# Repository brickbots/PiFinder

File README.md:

# PiFinder™
A plate solving telescope finder based around a Raspberry PI, imx296 camera, and custom UI 'hat'

For an overview of what the PiFinder™ is and how it came to be visit the official project website at [PiFinder.io](https://www.pifinder.io/build-yours) 

The PiFinder™ uses the [Cedar Detect](https://github.com/smroid/cedar-detect) and
[Cedar Solve](https://github.com/smroid/cedar-solve) libraries by
[smroid](https://github.com/smroid). Cedar Solve is licensed under Apache-2.0.

**Cedar Detect** is published under the Functional Source License (`FSL-1.1-MIT`),
which permits broad non-commercial use but excludes commercial uses that compete
with Cedar Detect. Because the PiFinder™ is also offered commercially, it bundles
and distributes the Cedar Detect binaries under a **separate license granted
expressly by the copyright holder** — not under the public FSL terms. The prebuilt
binaries live in [`bin/`](./bin/); see [`bin/README.md`](./bin/README.md) for the
full licensing details and a copy of the Cedar Detect license. Note this is
distinct from the PiFinder project's own GPL-3.0 [`LICENSE`](./LICENSE).

Thank you to [smroid](https://github.com/smroid) for all your support of the PiFinder project!

The PiFinder™ is my attempt to improve my time at my telescope.  I don't get nearly enough of it and I want to enjoy it as much as possible.  So after years of observing with paper charts and, later, a Nexus DSC here is what I felt I was missing:
* **Reliable telescope positioning:**  The Nexus DSC is great, but my scope just isn't built for solid encoder integration.  The slop in the way I have to couple the encoders means poor pointing accuracy.
* **Easy setup:**  The Nexus DSC needs multi-star alignment to understand how the encoders map to the sky.  The process is not terrible, but I'd like to avoid it.
* **Good push-to functionality**:  This is one place the Nexus DSC shines... if it's well aligned.  The catalog system is okay, and once you select and object the screen is clear and helpful to get the telescope pointed correctly.
* **Observation logging**:  I like to keep track of what I see each night.  I don't often sketch, just record what I saw when, with what eyepiece and some basic info about the experience.  If I could do this right at the eyepiece, that'd save time.

My hope is that other people will find this combination of functionality useful, will build their own PiFinder™ and help the whole project improve by making suggestions and potentially contributing to the software.  It's a pretty easy build with off the shelf parts and beginner friendly soldering.  

## Features
* Zero setup: Just turn it on and point it at the sky!  
* Accurate pointing: Onboard GPS determines location and time while the camera determines where the scope is pointing.  Inertial Measurement Unit tracks scope motion and updates sky position between camera solves
* Self-contained:  Includes catalog search/filtering, sky/object charting, push-to guidance and logging all via the screen and keypad on the unit.
* Dark site friendly:  Red OLED screen and soft backlit keys have wide brightness adjustment, right down to 'off'. No need for bright cell phones or tablets
* Easy access: Can be mounted by the eyepiece just like a finder.
- Wifi Access Point / SkySafari Integration:  The PiFinder™ can act as a WIFI access point to connect your tablet or phone to sync SkySafari or other planetarium software with your scope.

## Build Your Own
The PiFinder™ is fully open-source hardware and software.  You can order PCB's and 3d print the case with the files in this repo and order all the parts from the [parts List](https://pifinder.readthedocs.io/en/release/BOM.html).

If you would like pre-assembled units, kits or other items to jump start your PiFinder™ journey, visit [PiFinder.io](https://www.pifinder.io/build-pifinder) to see what's available and place an order.

## Docs

* [Quick Start](https://pifinder.readthedocs.io/en/release/quick_start.html)
* [User Manual](https://pifinder.readthedocs.io/en/release/user_guide.html)
* [Parts List](https://pifinder.readthedocs.io/en/release/BOM.html)
* [Build Guide](https://pifinder.readthedocs.io/en/release/build_guide.html)
* [Software Setup](https://pifinder.readthedocs.io/en/release/software.html)
* [Developer Guide](https://pifinder.readthedocs.io/en/release/dev_guide.html)

## Releases and Updates

If you are using a PiFinder, I recommend you watch releases in this repo.  Click the 'Watch' button up at the top right of the page, choose 'Custom' and then 'Releases' to make sure you don't miss any new features!

If you'd like to learn more about how it works, and potentially build your own, everything you need should be here.  I recommend starting with the [User Manual](https://pifinder.readthedocs.io/en/release/user_guide.html) and then checking out the build process using the links below.

## Discord
Join the  [PiFinder™ Discord server](https://discord.gg/Nk5fHcAtWD) for support with your build, usage questions, and suggestions for improvement.

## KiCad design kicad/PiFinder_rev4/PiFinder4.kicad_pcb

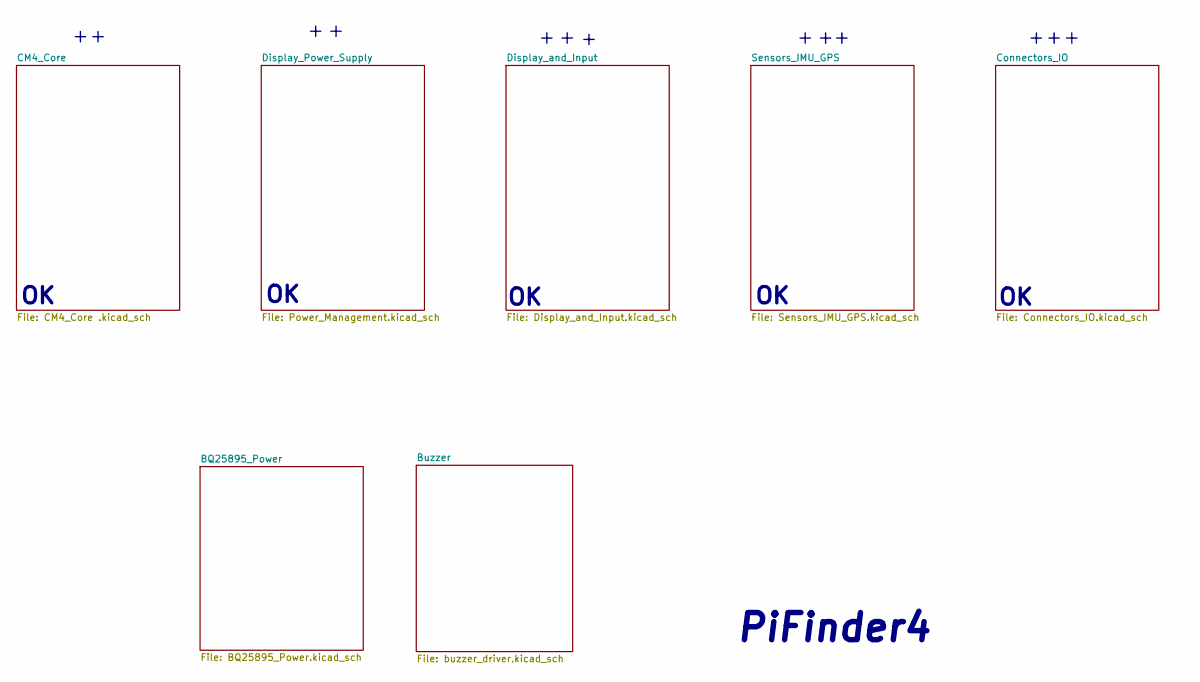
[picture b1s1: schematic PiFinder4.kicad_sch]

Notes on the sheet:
PiFinder4

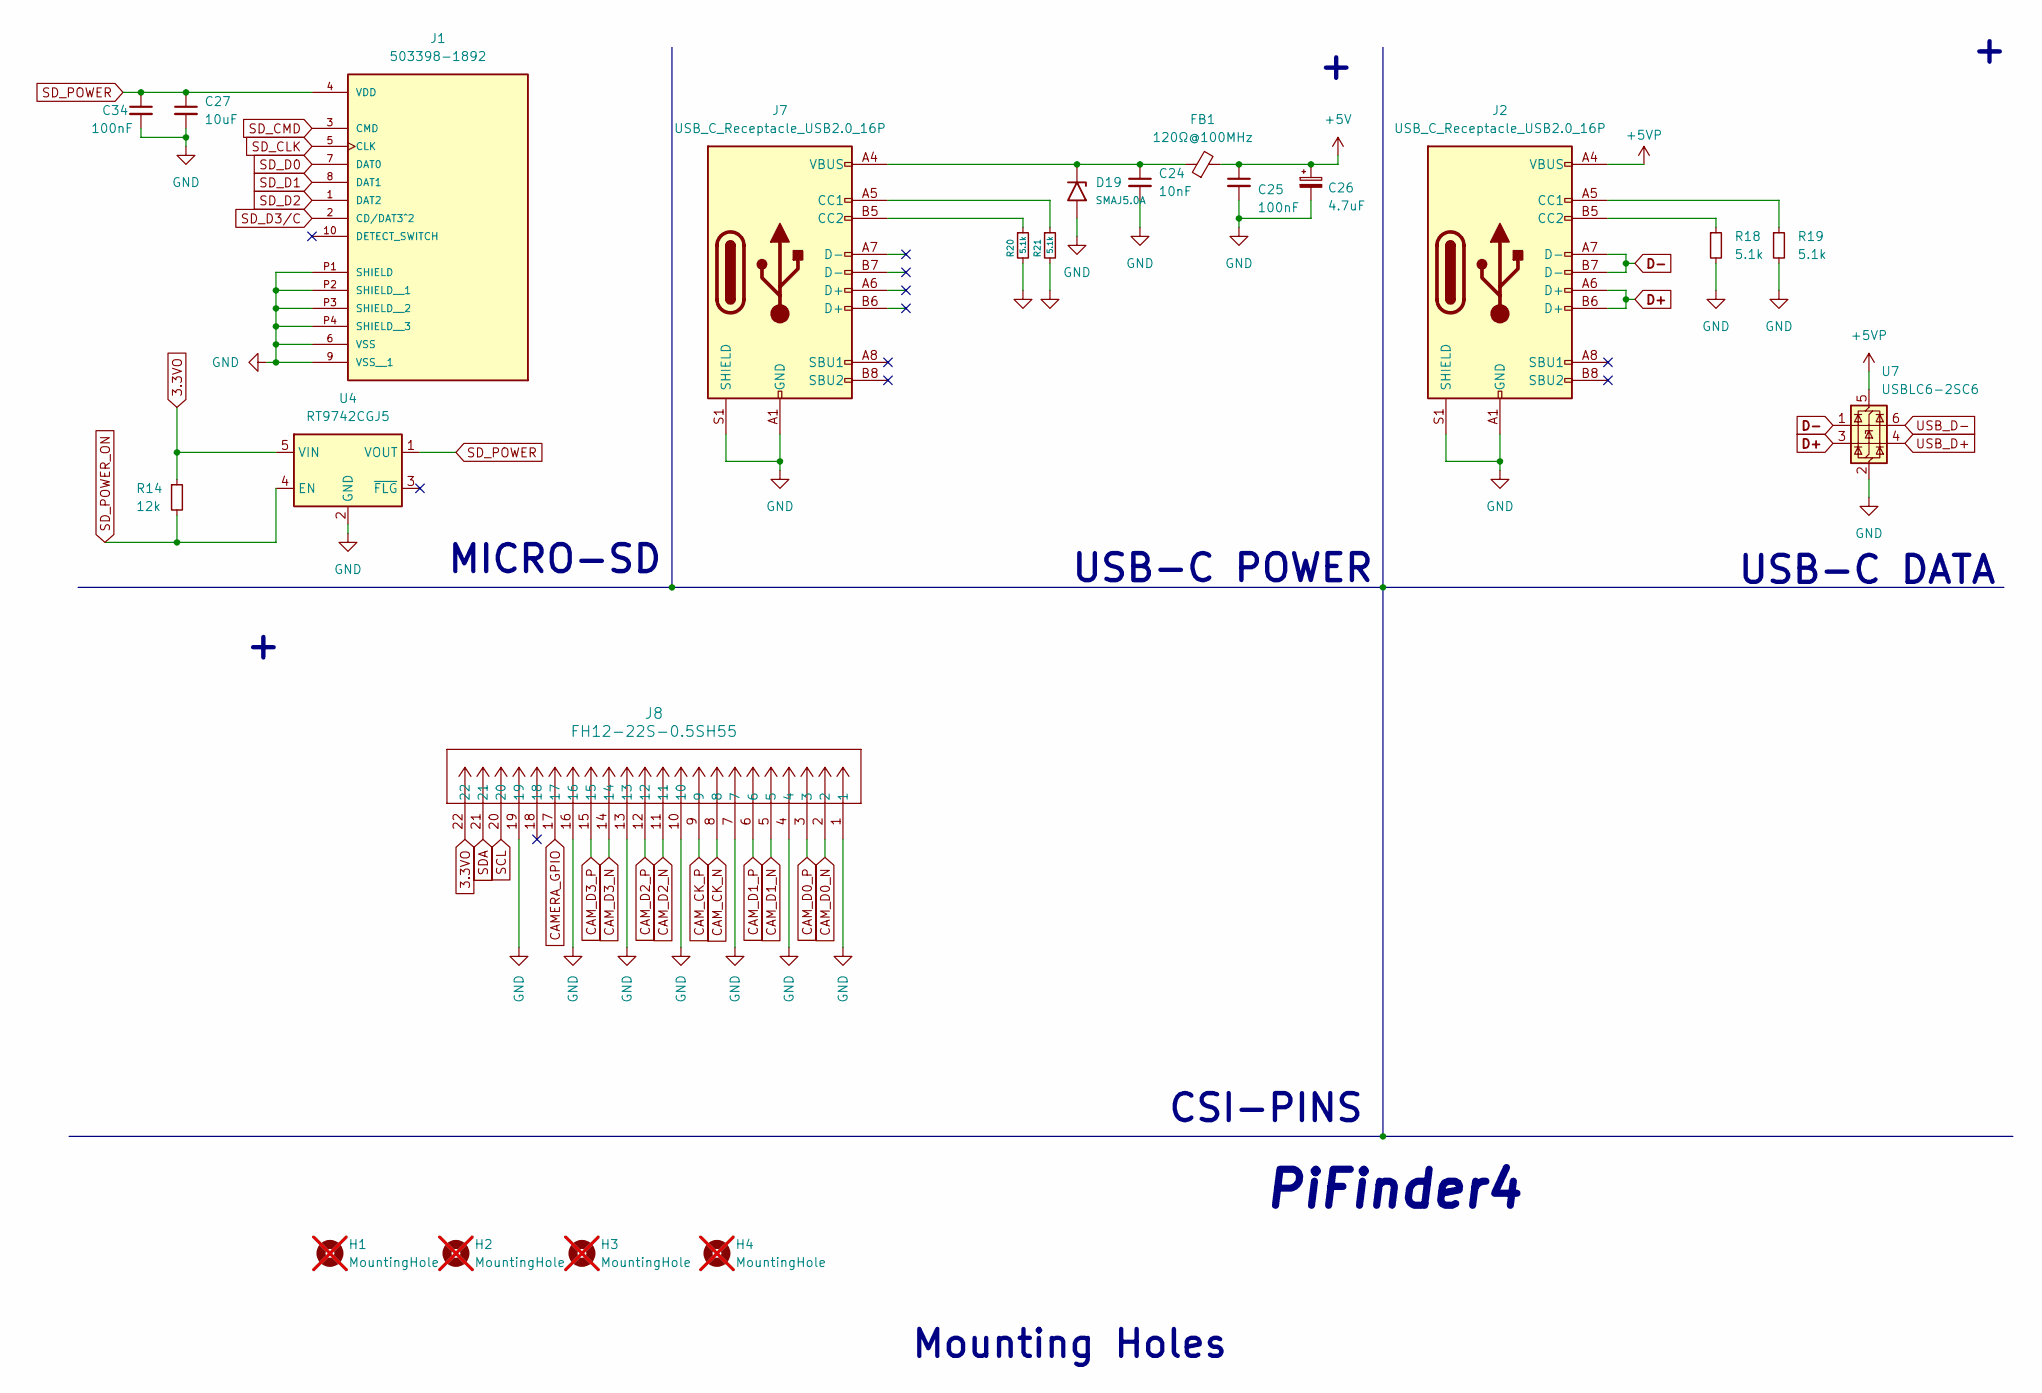
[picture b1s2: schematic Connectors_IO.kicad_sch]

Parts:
C24: 10nF; C_0402_1005Metric; LCSC C15195
C25, C34: 100nF; C_0603_1608Metric; LCSC C14663
C26: 4.7uF; CP_Elec_4x5.4; LCSC C970651
C27: 10uF; C_0805_2012Metric; LCSC C15850
D19: SMAJ5.0A; D_SMA; LCSC C10758
FB1: 120Ω@100MHz; L_1206_3216Metric; LCSC C85841
H1, H2, H3, H4: MountingHole; MountingHole_2.5mm; not fitted
J1: 503398-1892; MOLEX_503398-1892; PARTREV 0; LCSC C428492
J2, J7: USB_C_Receptacle_USB2.0_16P; USB_C_Receptacle_HCTL_HC-TYPE-C-16P-01A; LCSC C165948
J8: FH12-22S-0.5SH55; CONN_FH12-22S-0.5SH55_HIR; LCSC C597981
R14: 12k; R_0402_1005Metric; LCSC C25752
R18, R19, R20, R21: 5.1k; R_0402_1005Metric; LCSC C25905
U4: RT9742CGJ5; TSOT-23-5; LCSC C424402
U7: USBLC6-2SC6; SOT-23-6; LCSC C2687116

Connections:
3.3VO: J8.22, R14.1, U4.5 (VIN); also elsewhere on the board
+5V: C25.1, C26.1, FB1.2; also elsewhere on the board
+5VP: J2.A4 (VBUS), J2.A9 (VBUS), J2.B4 (VBUS), J2.B9 (VBUS), U7.5 (VBUS); also elsewhere on the board
CAMERA_GPIO: J8.17; also elsewhere on the board
CAM_CK_N: J8.8; also elsewhere on the board
CAM_CK_P: J8.9; also elsewhere on the board
CAM_D0_N: J8.2; also elsewhere on the board
CAM_D0_P: J8.3; also elsewhere on the board
CAM_D1_N: J8.5; also elsewhere on the board
CAM_D1_P: J8.6; also elsewhere on the board
CAM_D2_N: J8.11; also elsewhere on the board
CAM_D2_P: J8.12; also elsewhere on the board
CAM_D3_N: J8.14; also elsewhere on the board
CAM_D3_P: J8.15; also elsewhere on the board
D+: J2.A6 (D+), J2.B6 (D+), U7.3 (I/O2)
D-: J2.A7 (D-), J2.B7 (D-), U7.1 (I/O1)
GND: C24.2, C25.2, C26.2, C27.2, C34.2, D19.2 (A2), J1.6 (VSS), J1.9 (VSS__1), J1.P1 (SHIELD), J1.P2 (SHIELD__1), J1.P3 (SHIELD__2), J1.P4 (SHIELD__3), J2.A1 (GND), J2.A12 (GND), J2.B1 (GND), J2.B12 (GND), J2.S1 (SHIELD), J7.A1 (GND), J7.A12 (GND), J7.B1 (GND), J7.B12 (GND), J7.S1 (SHIELD), J8.1, J8.4, J8.7, J8.10, J8.13, J8.16, J8.19, R18.2, R19.2, R20.2, R21.2, U4.2 (GND), U7.2 (GND); also elsewhere on the board
unnamed: C24.1, D19.1 (A1), FB1.1, J7.A4 (VBUS), J7.A9 (VBUS), J7.B4 (VBUS), J7.B9 (VBUS)
unnamed: J2.A5 (CC1), R19.1
unnamed: J2.B5 (CC2), R18.1
unnamed: J7.A5 (CC1), R21.1
unnamed: J7.B5 (CC2), R20.1
SCL: J8.20; also elsewhere on the board
SDA: J8.21; also elsewhere on the board
SD_CLK: J1.5 (CLK); also elsewhere on the board
SD_CMD: J1.3 (CMD); also elsewhere on the board
SD_D0: J1.7 (DAT0); also elsewhere on the board
SD_D1: J1.8 (DAT1); also elsewhere on the board
SD_D2: J1.1 (DAT2); also elsewhere on the board
SD_D3/C: J1.2 (CD/DAT3^2); also elsewhere on the board
SD_POWER: C27.1, C34.1, J1.4 (VDD), U4.1 (VOUT)
SD_POWER_ON: R14.2, U4.4 (EN); also elsewhere on the board
USB_D+: U7.4 (I/O2); also elsewhere on the board
USB_D-: U7.6 (I/O1); also elsewhere on the board

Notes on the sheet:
CSI-PINS
USB-C DATA
PiFinder4
USB-C POWER
MICRO-SD
Mounting Holes

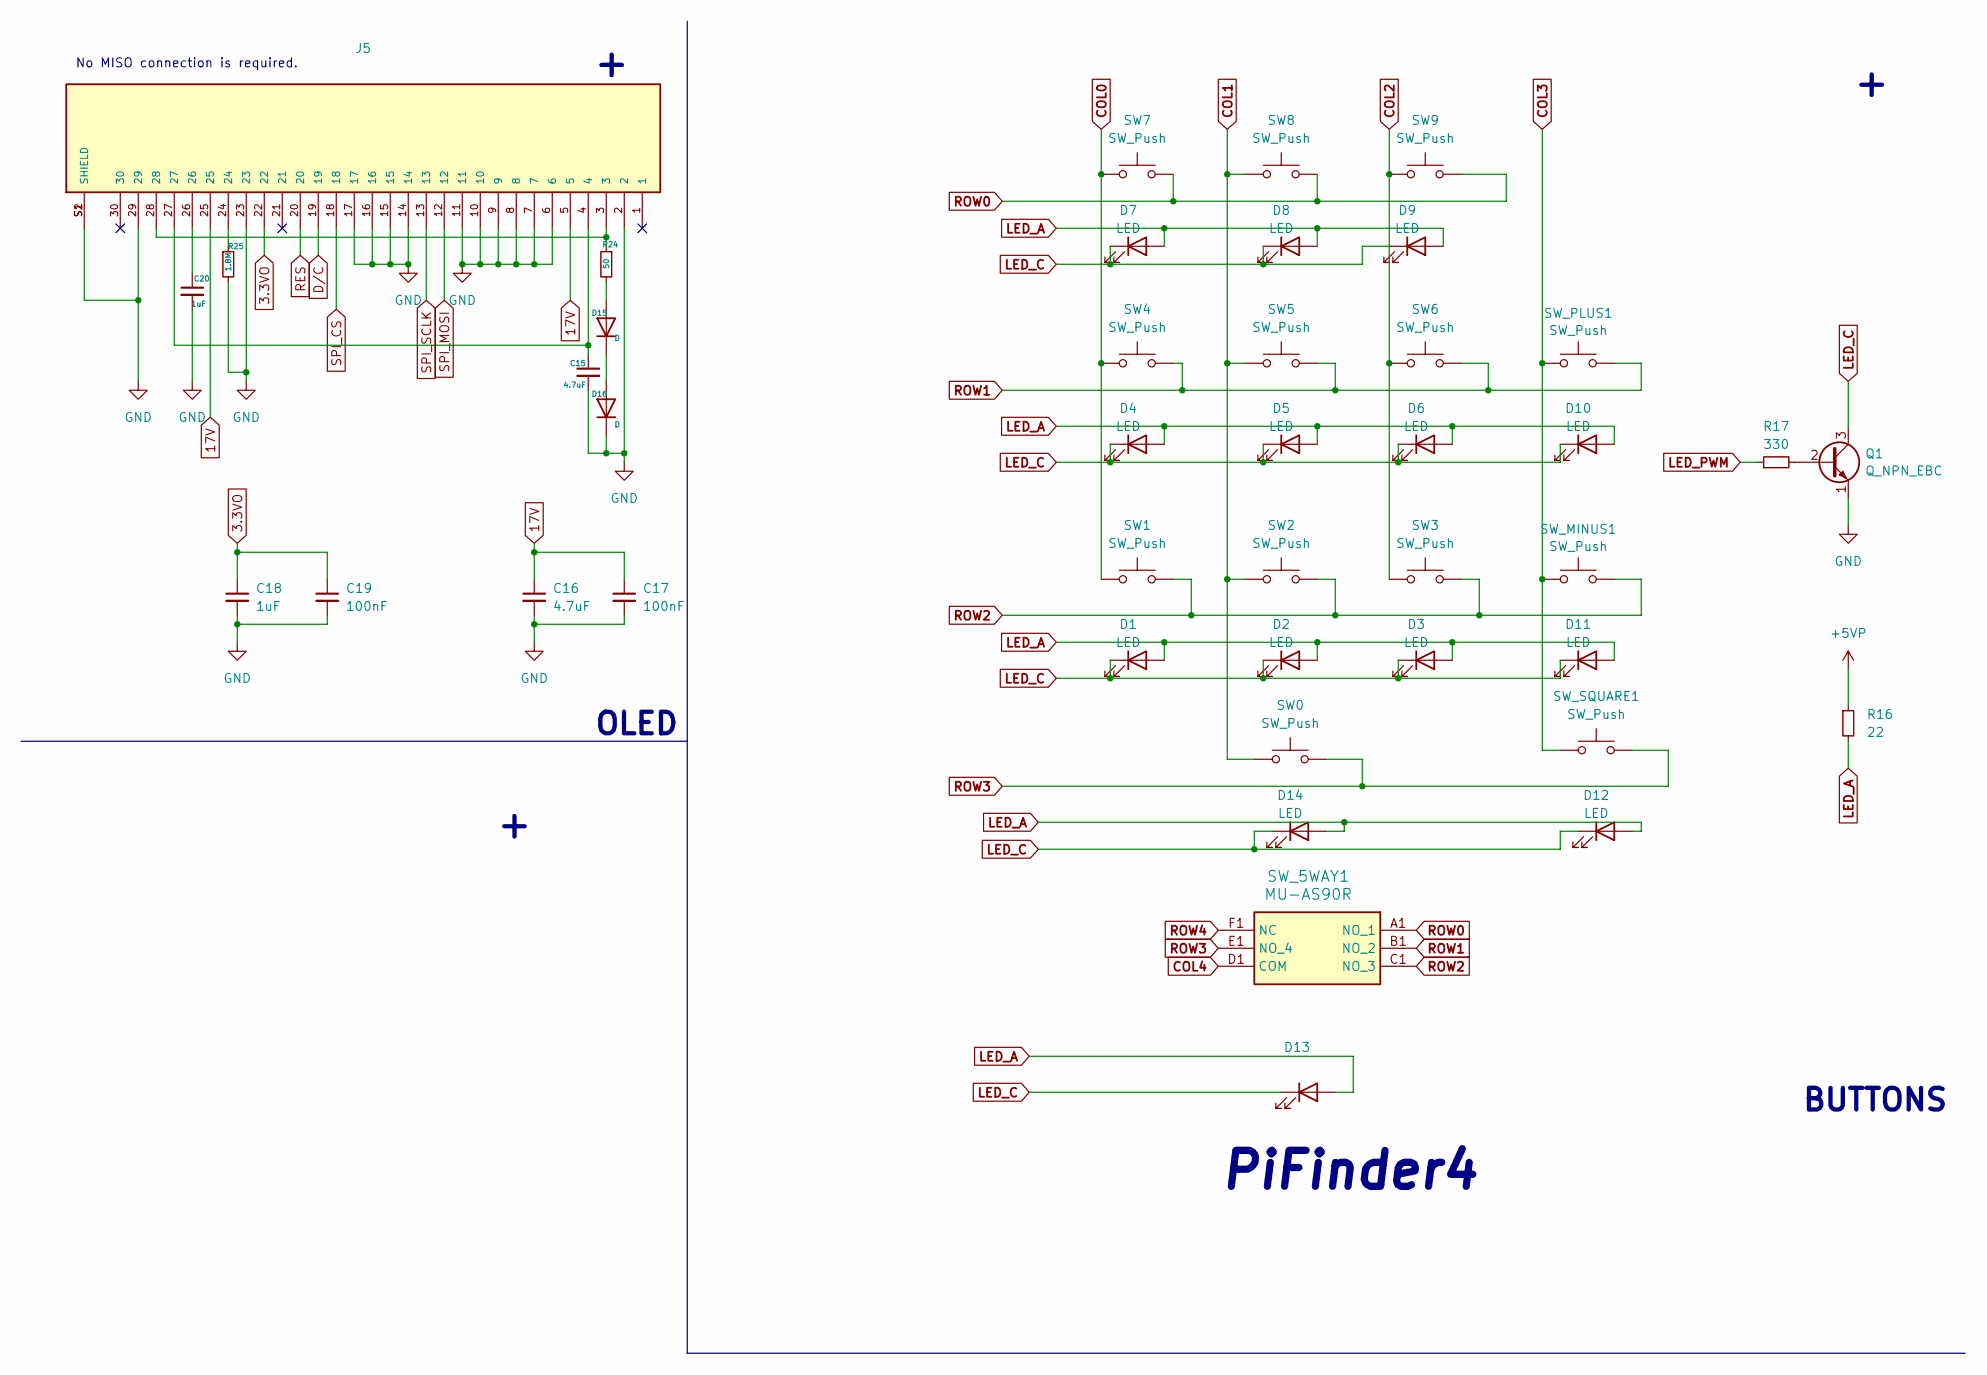
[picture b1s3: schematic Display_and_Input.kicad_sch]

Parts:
C15, C16: 4.7uF; C_1206_3216Metric; LCSC C29823
C17, C19: 100nF; C_0603_1608Metric; LCSC C14663
C18, C20: 1uF; C_0603_1608Metric; LCSC C15849
D1, D2, D3, D4, D5, D6, D7, D8, D9, D10, D11, D12, D13, D14: LED; LED_1210_3225Metric; LCSC C264578
D15, D16: D; D_SOD-123; LCSC C81598
J5: TE_3-1734592-0; PARTREV C; LCSC C375905
Q1: Q_NPN_EBC; PF_SOT-23-NPN; LCSC C280842
R16: 22; R_0402_1005Metric; LCSC C25092
R17: 330; R_0402_1005Metric; LCSC C25104
R24: 50; R_0603_1608Metric; LCSC C844932
R25: 1.8M; R_0402_1005Metric; LCSC C38587
SW0, SW1, SW2, SW3, SW4, SW5, SW6, SW7, SW8, SW9: SW_Push; SW_Push_6x6mm_SMT_withhole_tight; LCSC C4364377
SW_5WAY1: MU-AS90R; MUAS70R; Mouser Part Number 642-MU-AS70R; LCSC C38516684
SW_MINUS1: SW_Push; SW_Push_6x6mm_SMT_withhole_tight; LCSC C4364377
SW_PLUS1: SW_Push; SW_Push_6x6mm_SMT_withhole_tight; LCSC C4364377
SW_SQUARE1: SW_Push; SW_Push_6x6mm_SMT_withhole_tight; LCSC C4364377

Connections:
3.3VO: C18.1, C19.1, J5.22; also elsewhere on the board
17V: C16.1, C17.1, J5.5, J5.25; also elsewhere on the board
+5VP: R16.1; also elsewhere on the board
COL0: SW1.1, SW4.1, SW7.1; also elsewhere on the board
COL1: SW0.1, SW2.1, SW5.1, SW8.1; also elsewhere on the board
COL2: SW3.1, SW6.1, SW9.1; also elsewhere on the board
COL3: SW_MINUS1.1, SW_PLUS1.1, SW_SQUARE1.1; also elsewhere on the board
COL4: SW_5WAY1.D1 (COM); also elsewhere on the board
D/C: J5.19; also elsewhere on the board
GND: C15.2, C16.2, C17.2, C18.2, C19.2, C20.2, D16.1 (K), J5.2, J5.6, J5.7, J5.8, J5.9, J5.10, J5.11, J5.14, J5.15, J5.16, J5.17, J5.23, J5.29, J5.S1 (SHIELD), J5.S2 (SHIELD), Q1.1 (E), R25.2; also elsewhere on the board
LED_A: D1.2 (A), D2.2 (A), D3.2 (A), D4.2 (A), D5.2 (A), D6.2 (A), D7.2 (A), D8.2 (A), D9.2 (A), D10.2 (A), D11.2 (A), D12.2 (A), D13.2 (A), D14.2 (A), R16.2
LED_C: D1.1 (K), D2.1 (K), D3.1 (K), D4.1 (K), D5.1 (K), D6.1 (K), D7.1 (K), D8.1 (K), D9.1 (K), D10.1 (K), D11.1 (K), D12.1 (K), D13.1 (K), D14.1 (K), Q1.3 (C)
LED_PWM: R17.1; also elsewhere on the board
unnamed: C15.1, J5.4, J5.27
unnamed: C20.1, J5.26
unnamed: D15.2 (A), R24.2
unnamed: D15.1 (K), D16.2 (A)
unnamed: J5.24, R25.1
unnamed: J5.3, J5.28, R24.1
unnamed: Q1.2 (B), R17.2
RES: J5.20; also elsewhere on the board
ROW0: SW7.2, SW8.2, SW9.2, SW_5WAY1.A1 (NO_1); also elsewhere on the board
ROW1: SW4.2, SW5.2, SW6.2, SW_5WAY1.B1 (NO_2), SW_PLUS1.2; also elsewhere on the board
ROW2: SW1.2, SW2.2, SW3.2, SW_5WAY1.C1 (NO_3), SW_MINUS1.2; also elsewhere on the board
ROW3: SW0.2, SW_5WAY1.E1 (NO_4), SW_SQUARE1.2; also elsewhere on the board
ROW4: SW_5WAY1.F1 (NC); also elsewhere on the board
SPI_CS: J5.18; also elsewhere on the board
SPI_MOSI: J5.12; also elsewhere on the board
SPI_SCLK: J5.13; also elsewhere on the board

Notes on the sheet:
No MISO connection is required.
PiFinder4
BUTTONS
OLED

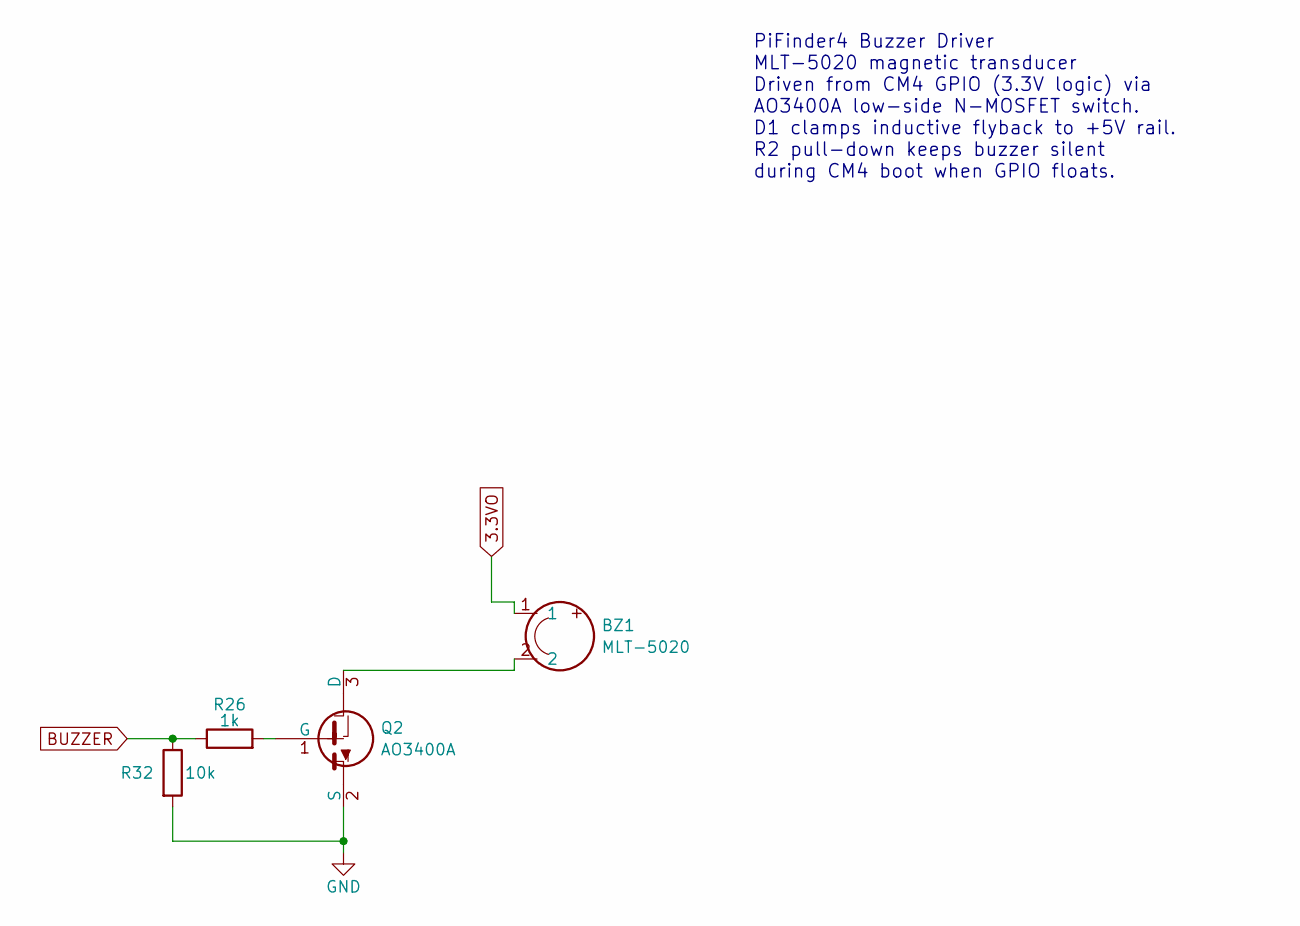
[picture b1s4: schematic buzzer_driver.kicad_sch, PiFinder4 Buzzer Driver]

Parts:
BZ1: MLT-5020; MagneticBuzzer_HuaWha_MLT-5020; LCSC C94598
Q2: AO3400A; SOT-23; LCSC C20917
R26: 1k; R_0402_1005Metric; LCSC C11702
R32: 10k; R_0402_1005Metric; LCSC C25744

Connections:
3.3VO: BZ1.1; also elsewhere on the board
BUZZER: R26.1, R32.1; also elsewhere on the board
GND: Q2.2 (S), R32.2; also elsewhere on the board
unnamed: BZ1.2, Q2.3 (D)
unnamed: Q2.1 (G), R26.2

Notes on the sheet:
PiFinder4 Buzzer Driver MLT-5020 magnetic transducer Driven from CM4 GPIO (3.3V logic) via AO3400A low-side N-MOSFET switch. D1 clamps inductive flyback to +5V rail. R2 pull-down keeps buzzer silent during CM4 boot when GPIO floats.

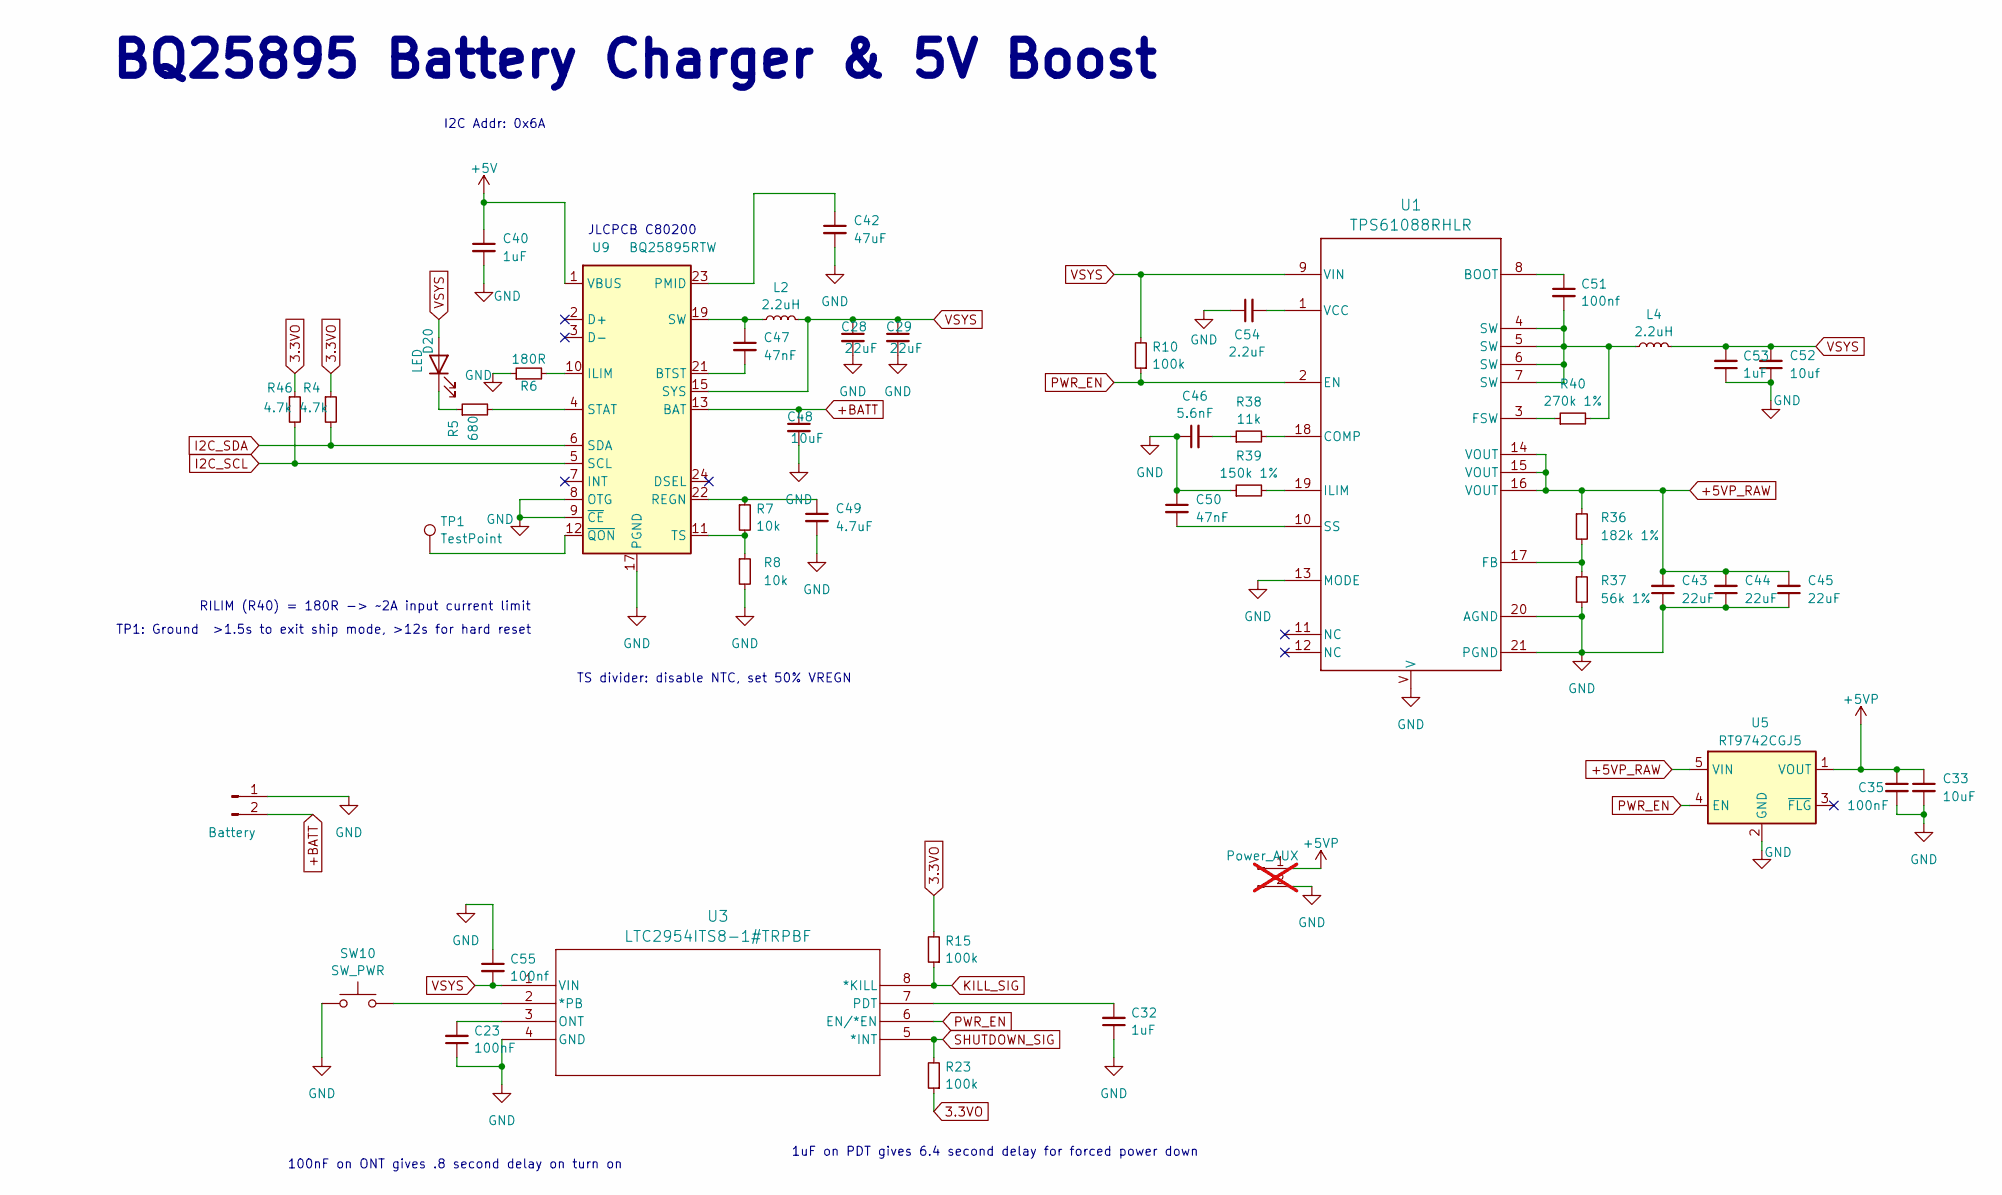
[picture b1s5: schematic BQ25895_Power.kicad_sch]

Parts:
C23, C35: 100nF; C_0603_1608Metric; LCSC C14663
C28, C29, C43, C44, C45: 22uF; C_0805_2012Metric; LCSC C45783
C32, C40, C53: 1uF; C_0603_1608Metric; LCSC C15849
C33: 10uF; C_0805_2012Metric; LCSC C15850
C42: 47uF; C_1206_3216Metric; LCSC C403725
C46: 5.6nF; C_0603_1608Metric; LCSC C107095
C47, C50: 47nF; C_0603_1608Metric; LCSC C1622
C48: 10uF; C_0603_1608Metric; LCSC C96446
C49: 4.7uF; C_0603_1608Metric; LCSC C19666
C51, C55: 100nf; C_0603_1608Metric; LCSC C14663
C52: 10uf; C_0805_2012Metric; LCSC C15850
C54: 2.2uF; C_0603_1608Metric; LCSC C23630
D20: LED; LED_1210_3225Metric; LCSC C264578
J3: Power_AUX; PinHeader_1x02_P2.54mm_Vertical; LCSC C160352; not fitted
J4: Battery; JST_PH_B2B-PH-SM4-TB_1x02-1MP_P2.00mm_Vertical; LCSC C160352
L2, L4: 2.2uH; L_Coilcraft_XAL4020-XXX; LCSC C3151182
R4, R46: 4.7k; R_0402_1005Metric; LCSC C25900
R5: 680; R_0402_1005Metric; LCSC C137948
R6: 180R; R_0402_1005Metric; LCSC C138045
R7, R8: 10k; R_0402_1005Metric; LCSC C25744
R10, R15, R23: 100k; R_0402_1005Metric; LCSC C25741
R36: 182k 1%; R_0402_1005Metric; LCSC C5159679
R37: 56k 1%; R_0402_1005Metric; LCSC C114756
R38: 11k; R_0402_1005Metric; LCSC C138063
R39: 150k 1%; R_0402_1005Metric; LCSC C2909320
R40: 270k 1%; R_0402_1005Metric; LCSC C25770
SW10: SW_PWR; SW_Push_6x6mm_SMT_withhole_tight; LCSC C4364377
TP1: TestPoint
U1: TPS61088RHLR; RHL0020A; LCSC C87357
U3: LTC2954ITS8-1#TRPBF; TSOT-23_TS8_LIT; LCSC C683782
U5: RT9742CGJ5; TSOT-23-5; LCSC C424402
U9: BQ25895RTW; Texas_RTW_WQFN-24-1EP_4x4mm_P0.5mm_EP2.7x2.7mm_ThermalVias; LCSC C80200

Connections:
3.3VO: R4.1, R15.2, R23.1, R46.1; also elsewhere on the board
+5V: C40.1, U9.1 (VBUS); also elsewhere on the board
+5VP: C33.1, C35.1, J3.1, U5.1 (VOUT); also elsewhere on the board
+5VP_RAW: C43.2, C44.2, C45.2, R36.1, U1.14 (VOUT), U1.15 (VOUT), U1.16 (VOUT), U5.5 (VIN)
+BATT: C48.1, J4.2, U9.13 (BAT), U9.14 (BAT)
GND: C23.1, C28.2, C29.2, C32.1, C33.2, C35.2, C40.2, C42.2, C43.1, C44.1, C45.1, C46.1, C48.2, C49.2, C50.1, C52.1, C53.1, C54.1, C55.1, J3.2, J4.1, R6.1, R8.2, R37.2, R39.1, SW10.1, U1.13 (MODE), U1.20 (AGND), U1.21 (PGND), U1.V, U3.4 (GND), U5.2 (GND), U9.8 (OTG), U9.9 (~CE), U9.17 (PGND), U9.18 (PGND), U9.25 (PGND); also elsewhere on the board
I2C_SCL: R46.2, U9.5 (SCL); also elsewhere on the board
I2C_SDA: R4.2, U9.6 (SDA); also elsewhere on the board
KILL_SIG: R15.1, U3.8 (*KILL); also elsewhere on the board
unnamed: C46.2, R38.1
unnamed: C47.1, L2.1, U9.19 (SW), U9.20 (SW)
unnamed: C51.2, L4.1, R40.2, U1.4 (SW), U1.5 (SW), U1.6 (SW), U1.7 (SW)
unnamed: D20.1 (K), R5.1
unnamed: C51.1, U1.8 (BOOT)
unnamed: R38.2, U1.18 (COMP)
unnamed: R36.2, R37.1, U1.17 (FB)
unnamed: R40.1, U1.3 (FSW)
unnamed: R39.2, U1.19 (ILIM)
unnamed: C50.2, U1.10 (SS)
unnamed: C54.2, U1.1 (VCC)
unnamed: SW10.2, U3.2 (*PB)
unnamed: C23.2, U3.3 (ONT)
unnamed: C32.2, U3.7 (PDT)
unnamed: C47.2, U9.21 (BTST)
unnamed: R6.2, U9.10 (ILIM)
unnamed: C42.1, U9.23 (PMID)
unnamed: C49.1, R7.1, U9.22 (REGN)
unnamed: R5.2, U9.4 (STAT)
unnamed: R7.2, R8.1, U9.11 (TS)
unnamed: TP1.1, U9.12 (~QON)
PWR_EN: R10.1, U1.2 (EN), U3.6 (EN/*EN), U5.4 (EN)
SHUTDOWN_SIG: R23.2, U3.5 (*INT); also elsewhere on the board
VSYS: C28.1, C29.1, C52.2, C53.2, C55.2, D20.2 (A), L2.2, L4.2, R10.2, U1.9 (VIN), U3.1 (VIN), U9.15 (SYS), U9.16 (SYS)

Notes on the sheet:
JLCPCB C80200
TS divider: disable NTC, set 50% VREGN
RILIM (R40) = 180R -> ~2A input current limit
TP1: Ground >1.5s to exit ship mode, >12s for hard reset
100nF on ONT gives .8 second delay on turn on
I2C Addr: 0x6A
BQ25895 Battery Charger & 5V Boost
1uF on PDT gives 6.4 second delay for forced power down

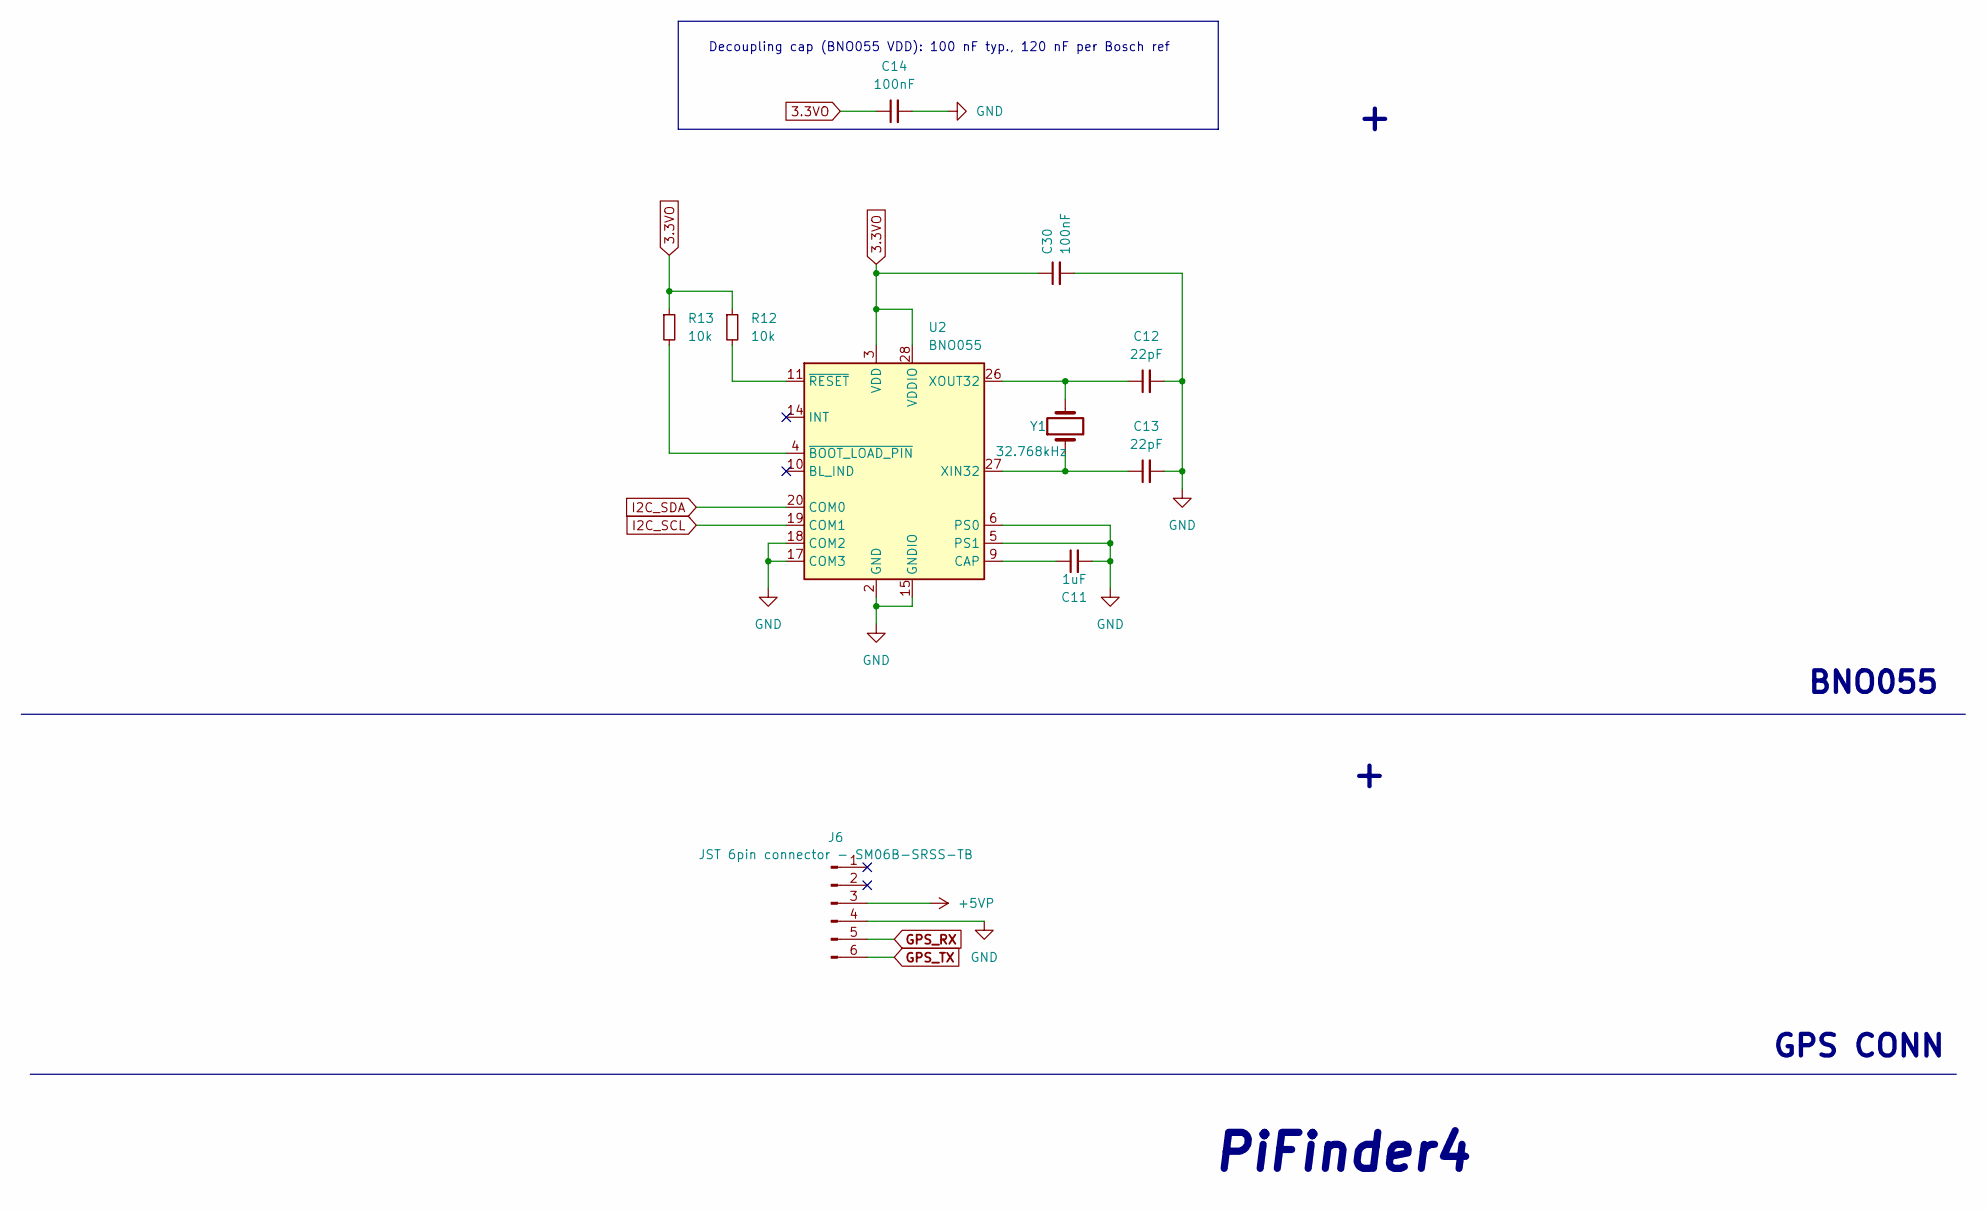
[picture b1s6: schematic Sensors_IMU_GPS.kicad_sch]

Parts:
C11: 1uF; C_0603_1608Metric; LCSC C15849
C12, C13: 22pF; C_0402_1005Metric; LCSC C1555
C14, C30: 100nF; C_0603_1608Metric; LCSC C14663
J6: JST 6pin connector - SM06B-SRSS-TB; JST_SH_BM06B-SRSS-TB_1x06-1MP_P1.00mm_Vertical; LCSC C160392
R12, R13: 10k; R_0402_1005Metric; LCSC C25744
U2: BNO055; LGA-28_5.2x3.8mm_P0.5mm; LCSC C93216
Y1: 32.768kHz; Crystal_SMD_3215-2Pin_3.2x1.5mm; LCSC C32346

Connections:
3.3VO: C14.1, C30.1, R12.1, R13.1, U2.3 (VDD), U2.28 (VDDIO); also elsewhere on the board
+5VP: J6.3; also elsewhere on the board
GND: C11.2, C12.2, C13.2, C14.2, C30.2, J6.4, U2.2 (GND), U2.5 (PS1), U2.6 (PS0), U2.15 (GNDIO), U2.16 (GNDIO), U2.17 (COM3), U2.18 (COM2), U2.25 (GNDIO); also elsewhere on the board
GPS_RX: J6.5; also elsewhere on the board
GPS_TX: J6.6; also elsewhere on the board
I2C_SCL: U2.19 (COM1); also elsewhere on the board
I2C_SDA: U2.20 (COM0); also elsewhere on the board
unnamed: C11.1, U2.9 (CAP)
unnamed: C13.1, U2.27 (XIN32), Y1.1
unnamed: C12.1, U2.26 (XOUT32), Y1.2
unnamed: R13.2, U2.4 (~BOOT_LOAD_PIN)
unnamed: R12.2, U2.11 (~RESET)

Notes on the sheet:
PiFinder4
Decoupling cap (BNO055 VDD): 100 nF typ., 120 nF per Bosch ref
GPS CONN
BNO055
